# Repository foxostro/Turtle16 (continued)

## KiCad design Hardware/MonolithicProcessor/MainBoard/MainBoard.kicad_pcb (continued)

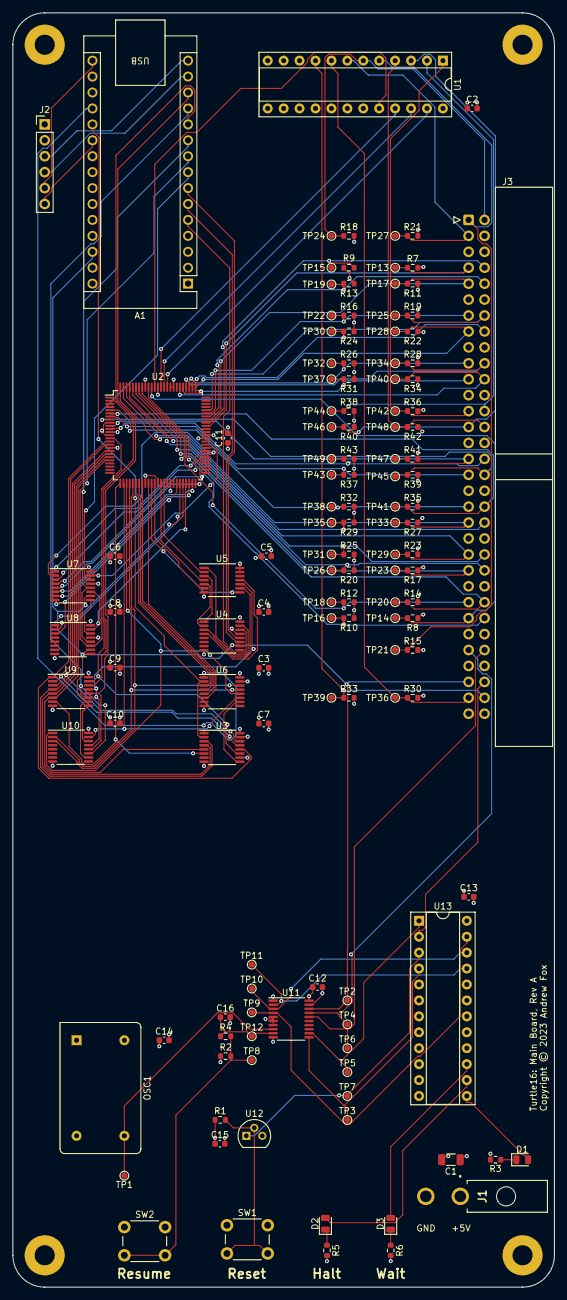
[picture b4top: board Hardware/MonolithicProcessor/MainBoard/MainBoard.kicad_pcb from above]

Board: 4 copper layers, 86.4 x 203.2 mm, 135 parts (0 on the bottom side), 119 nets.

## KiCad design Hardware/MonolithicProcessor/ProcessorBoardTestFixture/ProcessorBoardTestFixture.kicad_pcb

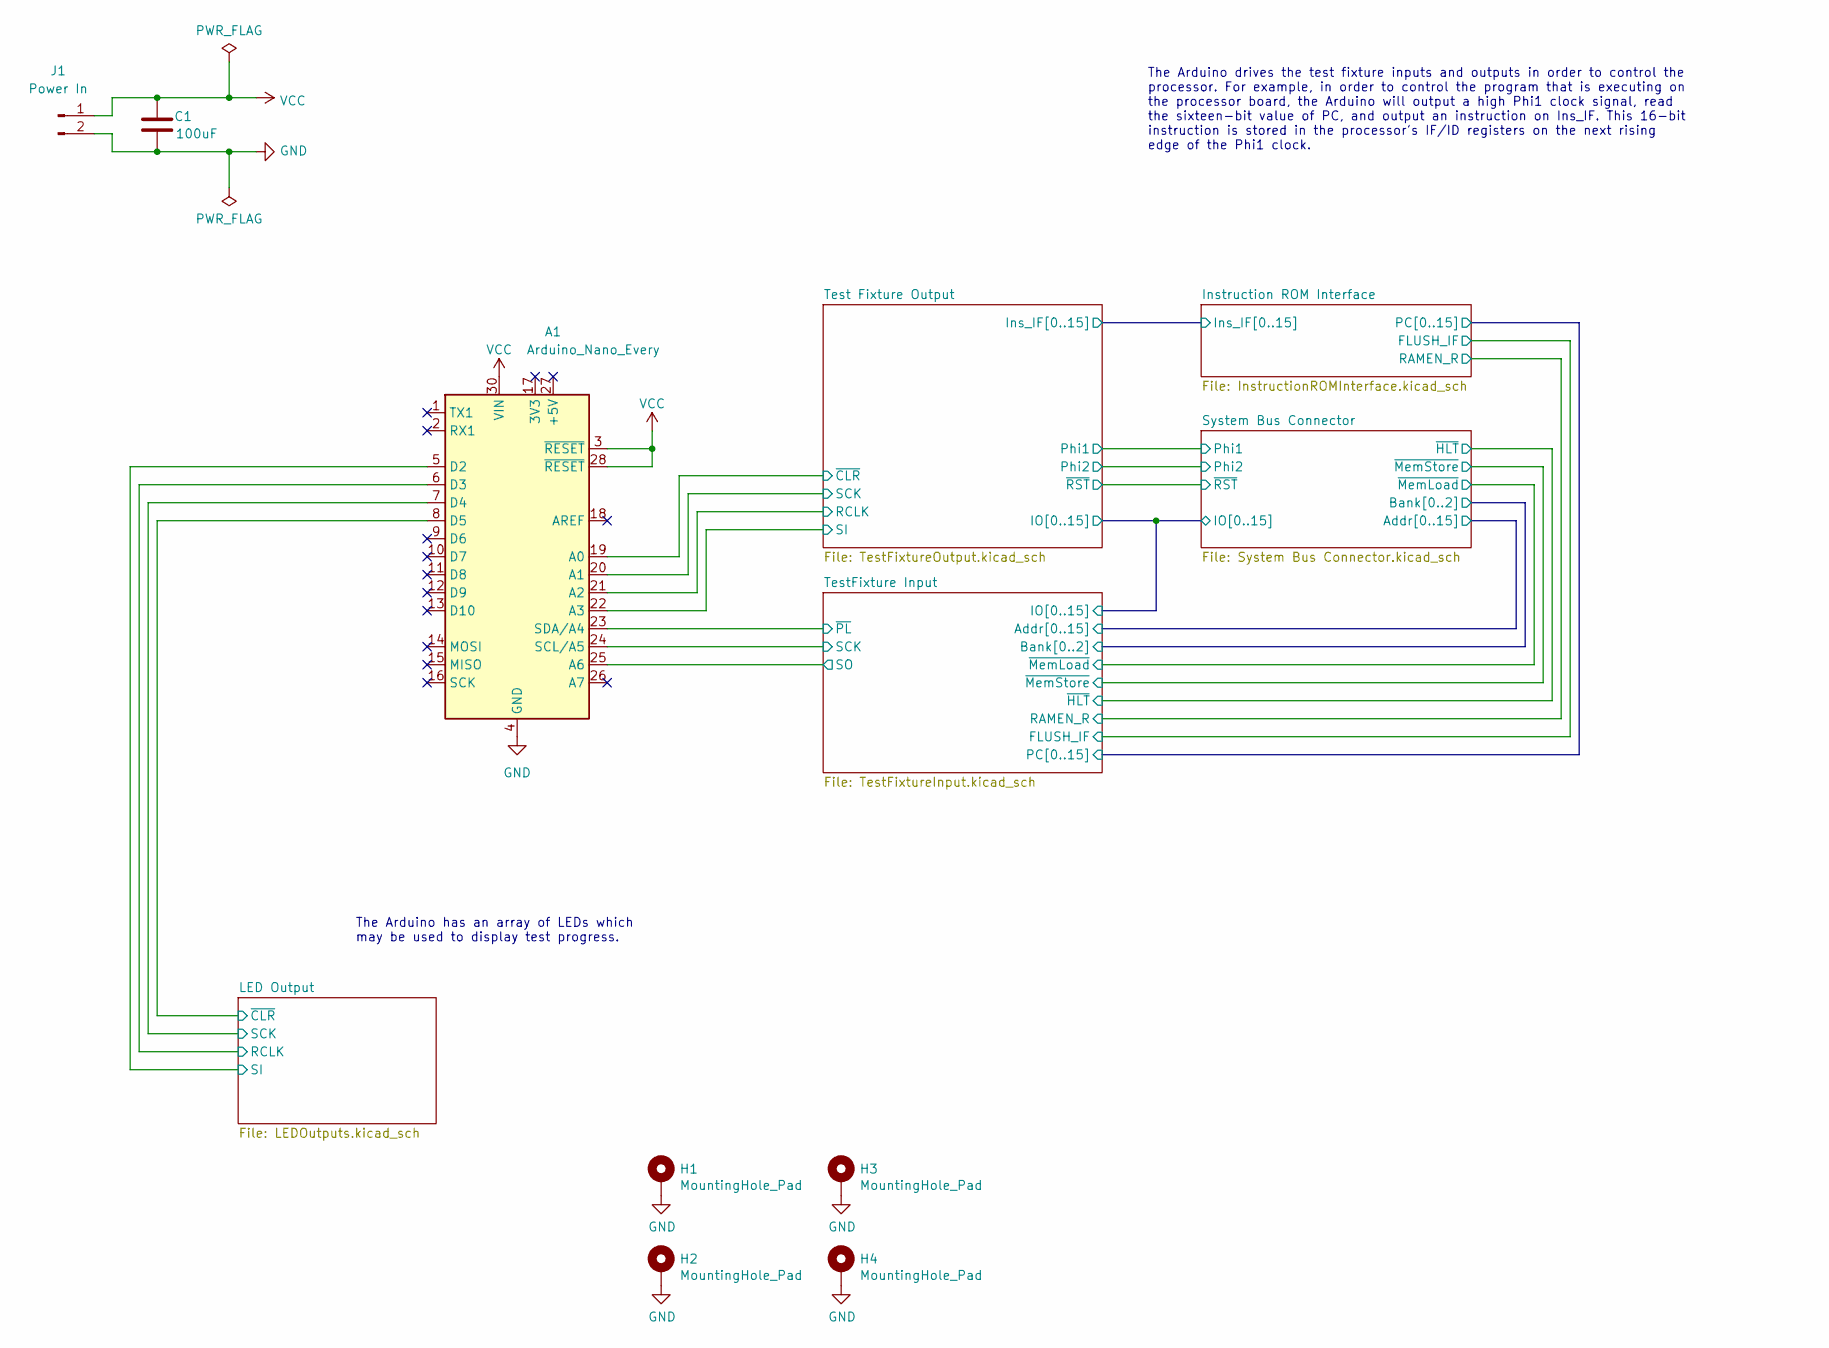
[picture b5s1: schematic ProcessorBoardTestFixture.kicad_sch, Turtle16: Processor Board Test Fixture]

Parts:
A1: Arduino_Nano_Every; Arduino_Nano
C1: 100uF; C_1206_3216Metric; Manufacturer# AMK316ABJ107ML-T; Mouser# 963-AMK316ABJ107ML-T
H1, H2, H3, H4: MountingHole_Pad; MountingHole_3.2mm_M3_Pad
J1: Power In; 172448-0002; Manufacturer# 172448-0002; Mouser# 538-172448-0002

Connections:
/LED Output/RCLK: A1.6 (D3); also elsewhere on the board
/LED Output/SCK: A1.7 (D4); also elsewhere on the board
/LED Output/SI: A1.5 (D2); also elsewhere on the board
/LED Output/~CLR: A1.8 (D5); also elsewhere on the board
/Test Fixture Output/RCLK: A1.21 (A2); also elsewhere on the board
/Test Fixture Output/SCK: A1.20 (A1); also elsewhere on the board
/Test Fixture Output/SI: A1.22 (A3); also elsewhere on the board
/Test Fixture Output/~CLR: A1.19 (A0); also elsewhere on the board
/TestFixture Input/SCK: A1.24 (SCL/A5); also elsewhere on the board
/TestFixture Input/SO: A1.25 (A6); also elsewhere on the board
/TestFixture Input/~PL: A1.23 (SDA/A4); also elsewhere on the board
GND: A1.4 (GND), A1.29 (GND), C1.2, H1.1, H2.1, H3.1, H4.1, J1.2; also elsewhere on the board
VCC: A1.3 (~RESET), A1.28 (~RESET), A1.30 (VIN), C1.1, J1.1; also elsewhere on the board

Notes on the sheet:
The Arduino has an array of LEDs which may be used to display test progress.
The Arduino drives the test fixture inputs and outputs in order to control the processor. For example, in order to control the program that is executing on the processor board, the Arduino will output a high Phi1 clock signal, read the sixteen-bit value of PC, and output an instruction on Ins_IF. T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

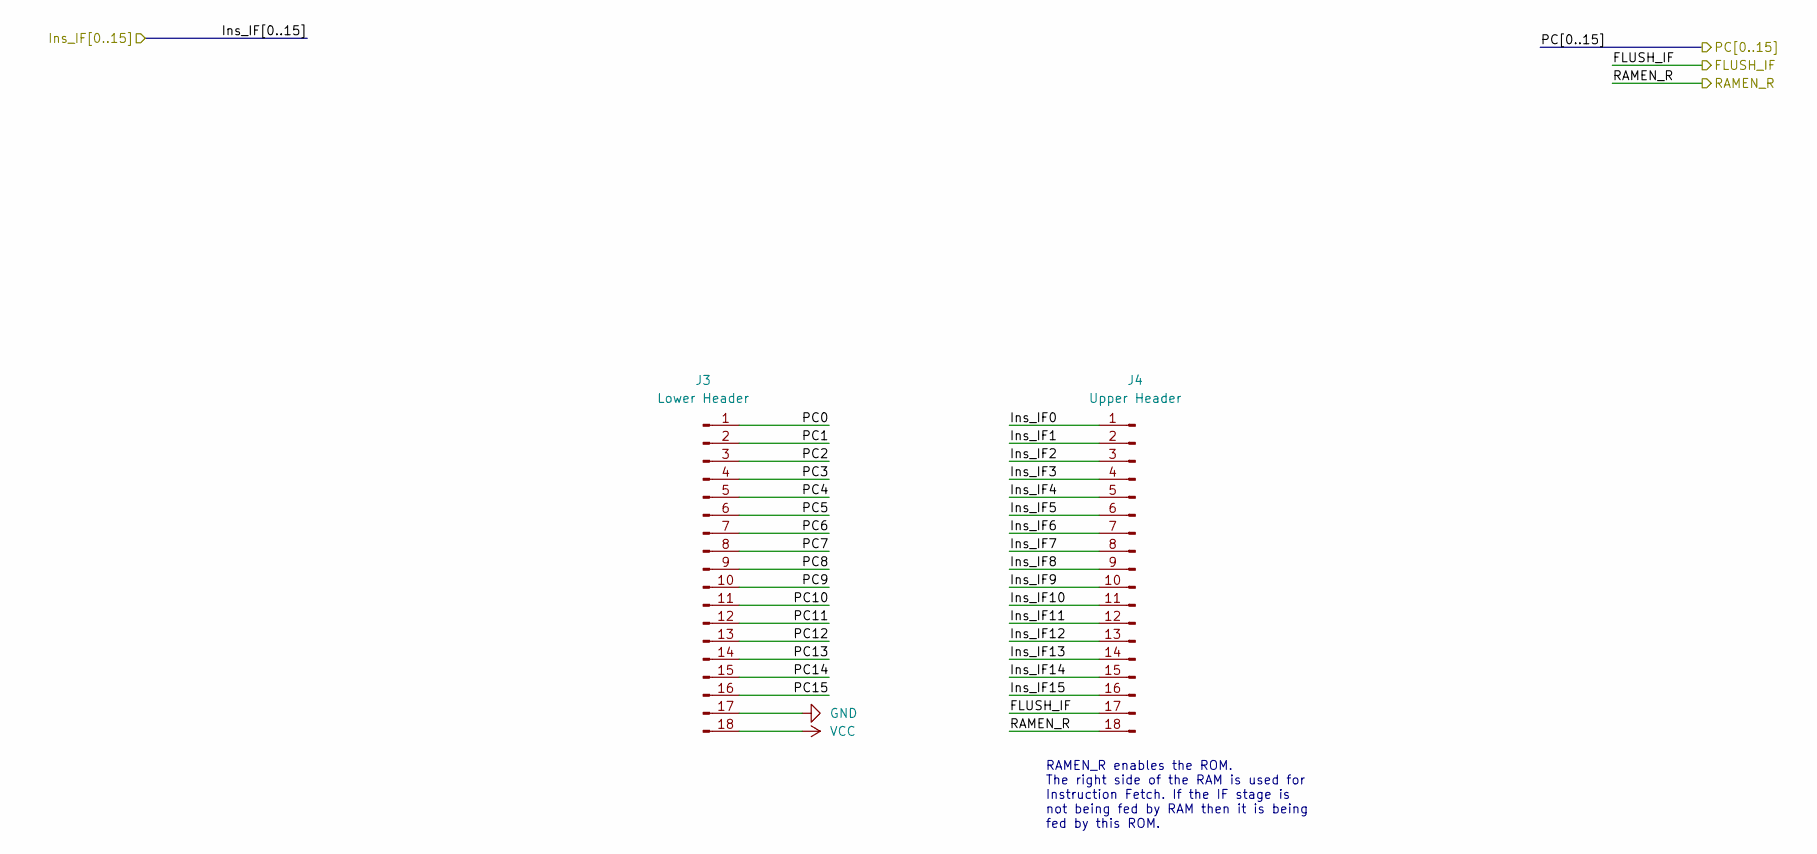
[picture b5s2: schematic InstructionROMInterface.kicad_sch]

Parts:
J3: Lower Header; PinHeader_1x18_P2.54mm_Vertical
J4: Upper Header; PinHeader_1x18_P2.54mm_Vertical

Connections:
/Instruction ROM Interface/FLUSH_IF: J4.17; also elsewhere on the board
/Instruction ROM Interface/Ins_IF0: J4.1; also elsewhere on the board
/Instruction ROM Interface/Ins_IF1: J4.2; also elsewhere on the board
/Instruction ROM Interface/Ins_IF2: J4.3; also elsewhere on the board
/Instruction ROM Interface/Ins_IF3: J4.4; also elsewhere on the board
/Instruction ROM Interface/Ins_IF4: J4.5; also elsewhere on the board
/Instruction ROM Interface/Ins_IF5: J4.6; also elsewhere on the board
/Instruction ROM Interface/Ins_IF6: J4.7; also elsewhere on the board
/Instruction ROM Interface/Ins_IF7: J4.8; also elsewhere on the board
/Instruction ROM Interface/Ins_IF8: J4.9; also elsewhere on the board
/Instruction ROM Interface/Ins_IF9: J4.10; also elsewhere on the board
/Instruction ROM Interface/Ins_IF10: J4.11; also elsewhere on the board
/Instruction ROM Interface/Ins_IF11: J4.12; also elsewhere on the board
/Instruction ROM Interface/Ins_IF12: J4.13; also elsewhere on the board
/Instruction ROM Interface/Ins_IF13: J4.14; also elsewhere on the board
/Instruction ROM Interface/Ins_IF14: J4.15; also elsewhere on the board
/Instruction ROM Interface/Ins_IF15: J4.16; also elsewhere on the board
/Instruction ROM Interface/PC0: J3.1; also elsewhere on the board
/Instruction ROM Interface/PC1: J3.2; also elsewhere on the board
/Instruction ROM Interface/PC2: J3.3; also elsewhere on the board
/Instruction ROM Interface/PC3: J3.4; also elsewhere on the board
/Instruction ROM Interface/PC4: J3.5; also elsewhere on the board
/Instruction ROM Interface/PC5: J3.6; also elsewhere on the board
/Instruction ROM Interface/PC6: J3.7; also elsewhere on the board
/Instruction ROM Interface/PC7: J3.8; also elsewhere on the board
/Instruction ROM Interface/PC8: J3.9; also elsewhere on the board
/Instruction ROM Interface/PC9: J3.10; also elsewhere on the board
/Instruction ROM Interface/PC10: J3.11; also elsewhere on the board
/Instruction ROM Interface/PC11: J3.12; also elsewhere on the board
/Instruction ROM Interface/PC12: J3.13; also elsewhere on the board
/Instruction ROM Interface/PC13: J3.14; also elsewhere on the board
/Instruction ROM Interface/PC14: J3.15; also elsewhere on the board
/Instruction ROM Interface/PC15: J3.16; also elsewhere on the board
/Instruction ROM Interface/RAMEN_R: J4.18; also elsewhere on the board
GND: J3.17; also elsewhere on the board
VCC: J3.18; also elsewhere on the board

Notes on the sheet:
RAMEN_R enables the ROM. The right side of the RAM is used for Instruction Fetch. If the IF stage is not being fed by RAM then it is being fed by this ROM.

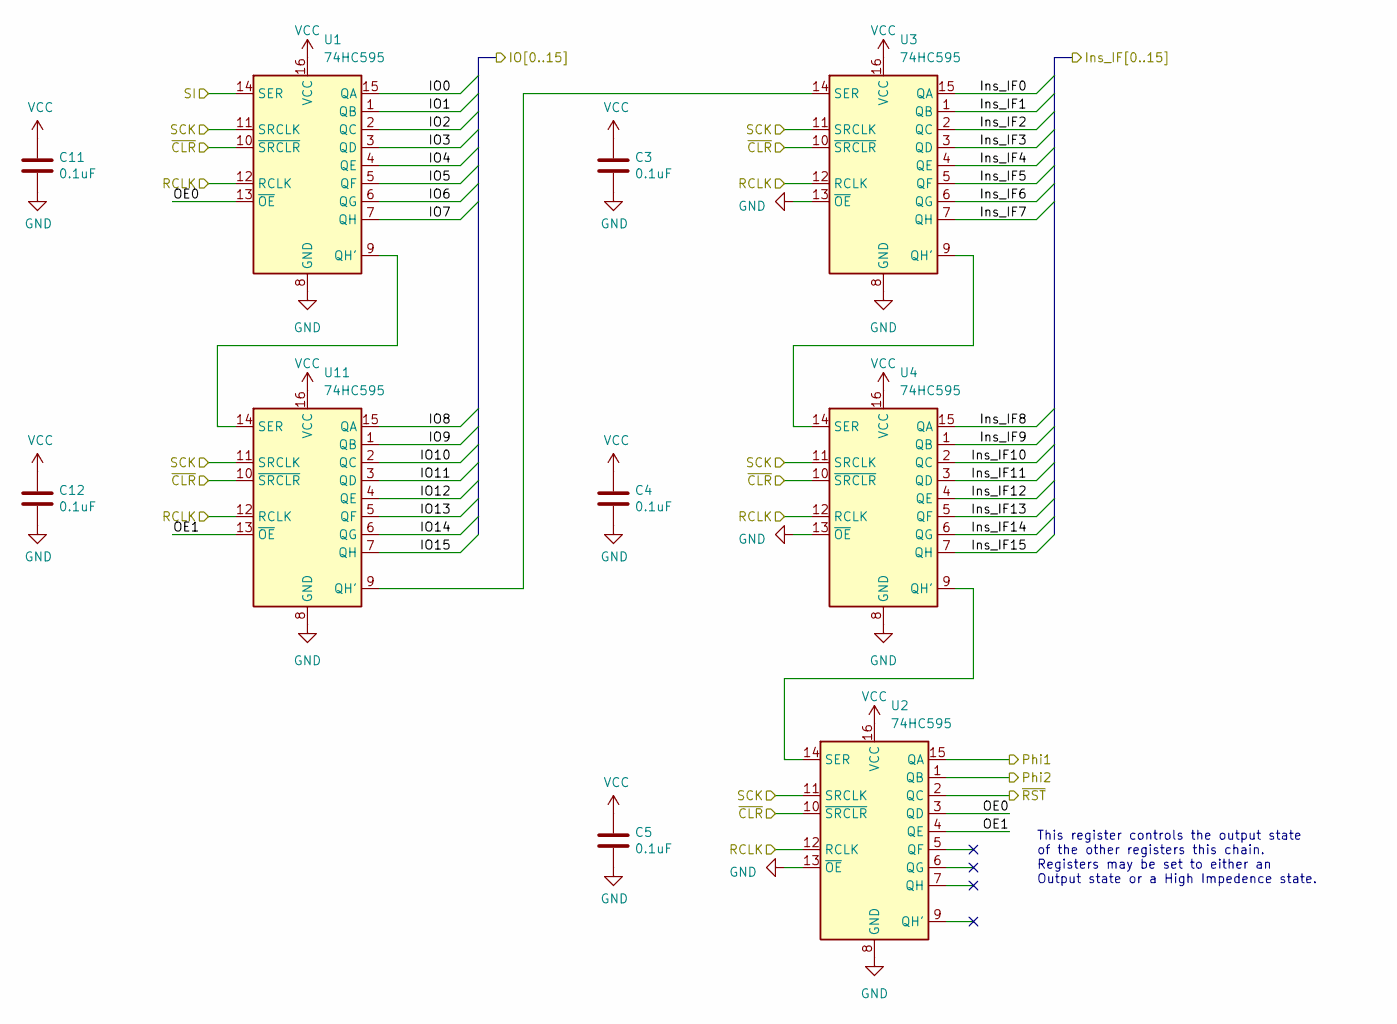
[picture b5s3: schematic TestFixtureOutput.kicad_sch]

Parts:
C3, C4, C5, C11, C12: 0.1uF; C_0603_1608Metric; Manufacturer# EMK107B7104KAHT; Mouser# 963-EMK107B7104KAHT
U1, U2, U3, U4, U11: 74HC595; TSSOP-16_4.4x5mm_P0.65mm; Manufacturer# 74HC595PW-Q100,118; Mouser# 771-74HC595PW-Q100

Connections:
/Instruction ROM Interface/Ins_IF0: U3.15 (QA); also elsewhere on the board
/Instruction ROM Interface/Ins_IF1: U3.1 (QB); also elsewhere on the board
/Instruction ROM Interface/Ins_IF2: U3.2 (QC); also elsewhere on the board
/Instruction ROM Interface/Ins_IF3: U3.3 (QD); also elsewhere on the board
/Instruction ROM Interface/Ins_IF4: U3.4 (QE); also elsewhere on the board
/Instruction ROM Interface/Ins_IF5: U3.5 (QF); also elsewhere on the board
/Instruction ROM Interface/Ins_IF6: U3.6 (QG); also elsewhere on the board
/Instruction ROM Interface/Ins_IF7: U3.7 (QH); also elsewhere on the board
/Instruction ROM Interface/Ins_IF8: U4.15 (QA); also elsewhere on the board
/Instruction ROM Interface/Ins_IF9: U4.1 (QB); also elsewhere on the board
/Instruction ROM Interface/Ins_IF10: U4.2 (QC); also elsewhere on the board
/Instruction ROM Interface/Ins_IF11: U4.3 (QD); also elsewhere on the board
/Instruction ROM Interface/Ins_IF12: U4.4 (QE); also elsewhere on the board
/Instruction ROM Interface/Ins_IF13: U4.5 (QF); also elsewhere on the board
/Instruction ROM Interface/Ins_IF14: U4.6 (QG); also elsewhere on the board
/Instruction ROM Interface/Ins_IF15: U4.7 (QH); also elsewhere on the board
/System Bus Connector/IO0: U1.15 (QA); also elsewhere on the board
/System Bus Connector/IO1: U1.1 (QB); also elsewhere on the board
/System Bus Connector/IO2: U1.2 (QC); also elsewhere on the board
/System Bus Connector/IO3: U1.3 (QD); also elsewhere on the board
/System Bus Connector/IO4: U1.4 (QE); also elsewhere on the board
/System Bus Connector/IO5: U1.5 (QF); also elsewhere on the board
/System Bus Connector/IO6: U1.6 (QG); also elsewhere on the board
/System Bus Connector/IO7: U1.7 (QH); also elsewhere on the board
/System Bus Connector/IO8: U11.15 (QA); also elsewhere on the board
/System Bus Connector/IO9: U11.1 (QB); also elsewhere on the board
/System Bus Connector/IO10: U11.2 (QC); also elsewhere on the board
/System Bus Connector/IO11: U11.3 (QD); also elsewhere on the board
/System Bus Connector/IO12: U11.4 (QE); also elsewhere on the board
/System Bus Connector/IO13: U11.5 (QF); also elsewhere on the board
/System Bus Connector/IO14: U11.6 (QG); also elsewhere on the board
/System Bus Connector/IO15: U11.7 (QH); also elsewhere on the board
/System Bus Connector/Phi1: U2.15 (QA); also elsewhere on the board
/System Bus Connector/Phi2: U2.1 (QB); also elsewhere on the board
/System Bus Connector/~RST: U2.2 (QC); also elsewhere on the board
/Test Fixture Output/OE0: U1.13 (~OE), U2.3 (QD)
/Test Fixture Output/OE1: U2.4 (QE), U11.13 (~OE)
/Test Fixture Output/RCLK: U1.12 (RCLK), U2.12 (RCLK), U3.12 (RCLK), U4.12 (RCLK), U11.12 (RCLK); also elsewhere on the board
/Test Fixture Output/SCK: U1.11 (SRCLK), U2.11 (SRCLK), U3.11 (SRCLK), U4.11 (SRCLK), U11.11 (SRCLK); also elsewhere on the board
/Test Fixture Output/SI: U1.14 (SER); also elsewhere on the board
/Test Fixture Output/~CLR: U1.10 (~SRCLR), U2.10 (~SRCLR), U3.10 (~SRCLR), U4.10 (~SRCLR), U11.10 (~SRCLR); also elsewhere on the board
GND: C3.2, C4.2, C5.2, C11.2, C12.2, U1.8 (GND), U2.8 (GND), U2.13 (~OE), U3.8 (GND), U3.13 (~OE), U4.8 (GND), U4.13 (~OE), U11.8 (GND); also elsewhere on the board
unnamed: U1.9 (QH'), U11.14 (SER)
unnamed: U2.14 (SER), U4.9 (QH')
unnamed: U3.9 (QH'), U4.14 (SER)
unnamed: U3.14 (SER), U11.9 (QH')
VCC: C3.1, C4.1, C5.1, C11.1, C12.1, U1.16 (VCC), U2.16 (VCC), U3.16 (VCC), U4.16 (VCC), U11.16 (VCC); also elsewhere on the board

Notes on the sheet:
This register controls the output state of the other registers this chain. Registers may be set to either an Output state or a High Impedence state.

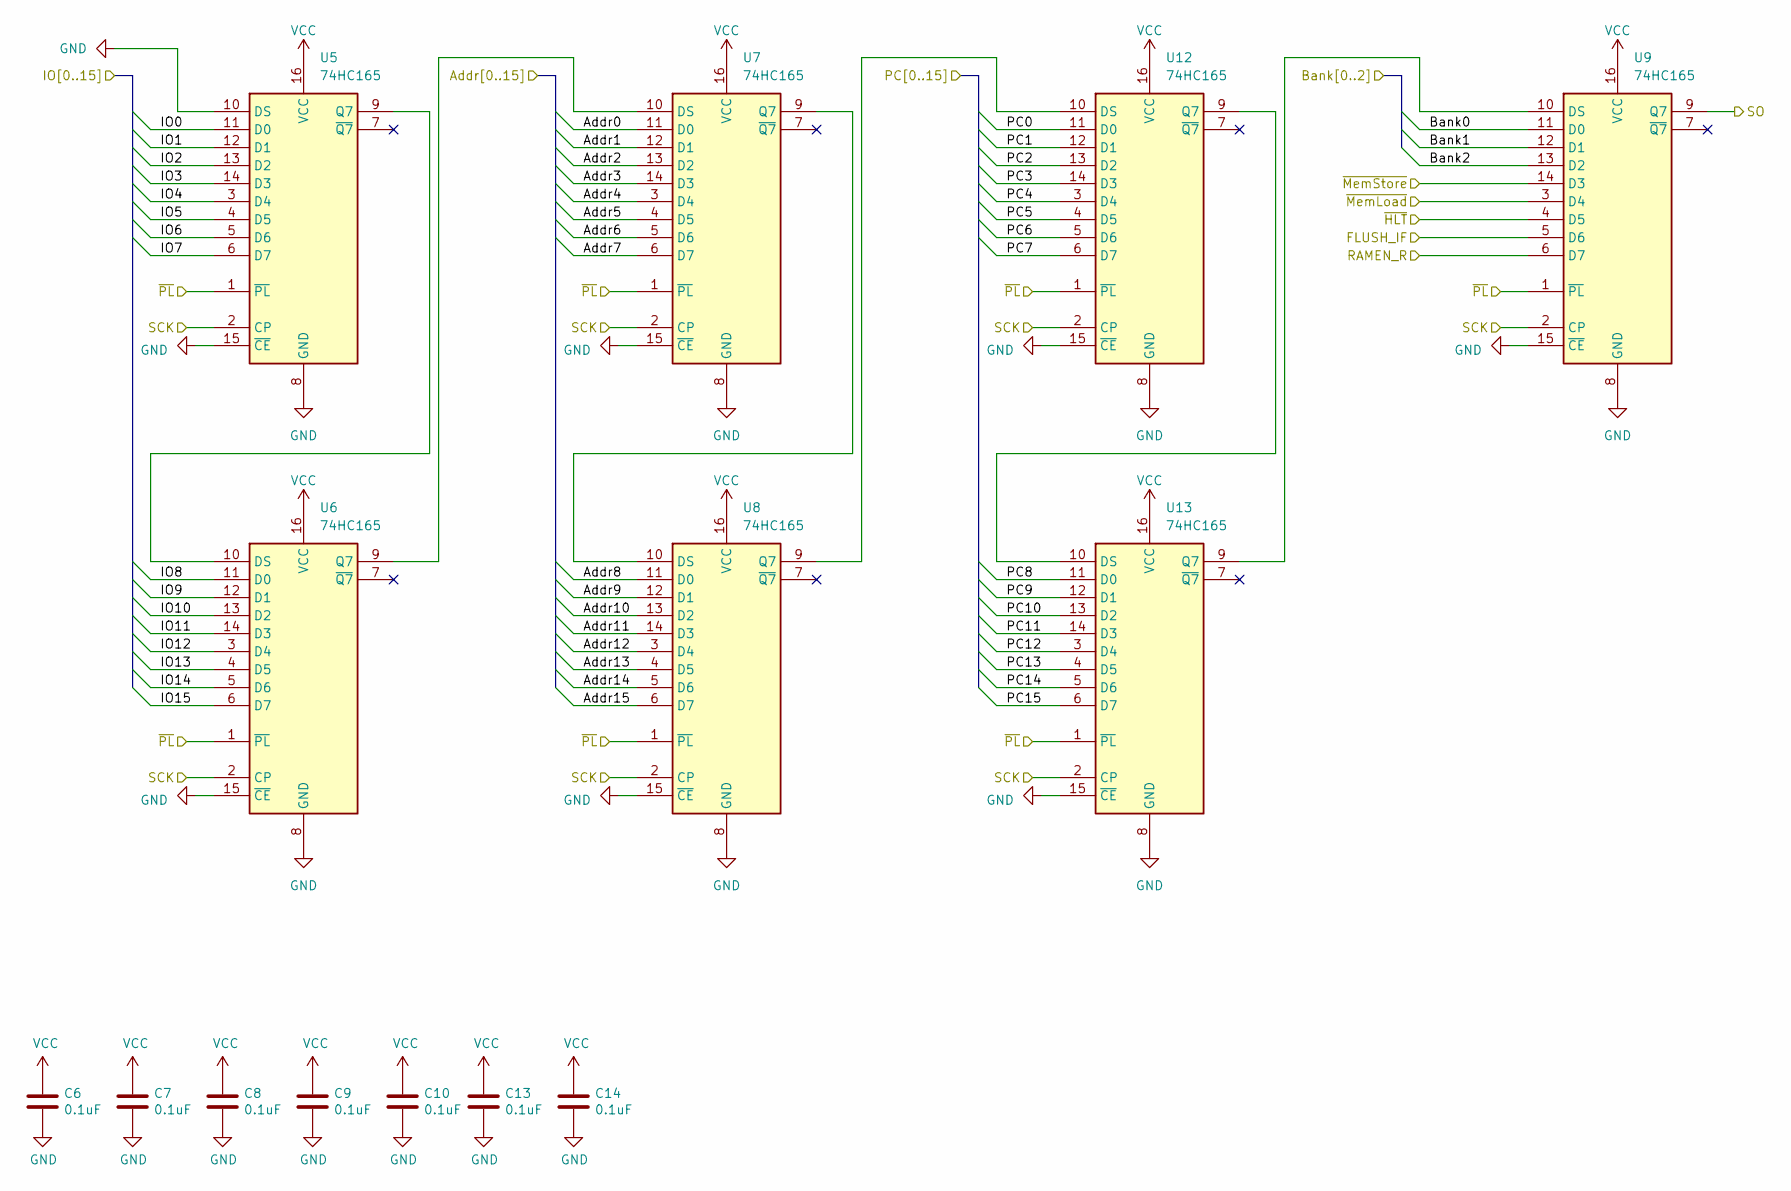
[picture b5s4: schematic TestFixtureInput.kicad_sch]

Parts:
C6, C7, C8, C9, C10, C13, C14: 0.1uF; C_0603_1608Metric; Manufacturer# EMK107B7104KAHT; Mouser# 963-EMK107B7104KAHT
U5, U6, U7, U8, U9, U12, U13: 74HC165; TSSOP-16_4.4x5mm_P0.65mm; Manufacturer# 74HC165PW-Q100,118; Mouser# 771-74HC165PWQ100118

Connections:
/Instruction ROM Interface/FLUSH_IF: U9.5 (D6); also elsewhere on the board
/Instruction ROM Interface/PC0: U12.11 (D0); also elsewhere on the board
/Instruction ROM Interface/PC1: U12.12 (D1); also elsewhere on the board
/Instruction ROM Interface/PC2: U12.13 (D2); also elsewhere on the board
/Instruction ROM Interface/PC3: U12.14 (D3); also elsewhere on the board
/Instruction ROM Interface/PC4: U12.3 (D4); also elsewhere on the board
/Instruction ROM Interface/PC5: U12.4 (D5); also elsewhere on the board
/Instruction ROM Interface/PC6: U12.5 (D6); also elsewhere on the board
/Instruction ROM Interface/PC7: U12.6 (D7); also elsewhere on the board
/Instruction ROM Interface/PC8: U13.11 (D0); also elsewhere on the board
/Instruction ROM Interface/PC9: U13.12 (D1); also elsewhere on the board
/Instruction ROM Interface/PC10: U13.13 (D2); also elsewhere on the board
/Instruction ROM Interface/PC11: U13.14 (D3); also elsewhere on the board
/Instruction ROM Interface/PC12: U13.3 (D4); also elsewhere on the board
/Instruction ROM Interface/PC13: U13.4 (D5); also elsewhere on the board
/Instruction ROM Interface/PC14: U13.5 (D6); also elsewhere on the board
/Instruction ROM Interface/PC15: U13.6 (D7); also elsewhere on the board
/Instruction ROM Interface/RAMEN_R: U9.6 (D7); also elsewhere on the board
/System Bus Connector/Addr0: U7.11 (D0); also elsewhere on the board
/System Bus Connector/Addr1: U7.12 (D1); also elsewhere on the board
/System Bus Connector/Addr2: U7.13 (D2); also elsewhere on the board
/System Bus Connector/Addr3: U7.14 (D3); also elsewhere on the board
/System Bus Connector/Addr4: U7.3 (D4); also elsewhere on the board
/System Bus Connector/Addr5: U7.4 (D5); also elsewhere on the board
/System Bus Connector/Addr6: U7.5 (D6); also elsewhere on the board
/System Bus Connector/Addr7: U7.6 (D7); also elsewhere on the board
/System Bus Connector/Addr8: U8.11 (D0); also elsewhere on the board
/System Bus Connector/Addr9: U8.12 (D1); also elsewhere on the board
/System Bus Connector/Addr10: U8.13 (D2); also elsewhere on the board
/System Bus Connector/Addr11: U8.14 (D3); also elsewhere on the board
/System Bus Connector/Addr12: U8.3 (D4); also elsewhere on the board
/System Bus Connector/Addr13: U8.4 (D5); also elsewhere on the board
/System Bus Connector/Addr14: U8.5 (D6); also elsewhere on the board
/System Bus Connector/Addr15: U8.6 (D7); also elsewhere on the board
/System Bus Connector/Bank0: U9.11 (D0); also elsewhere on the board
/System Bus Connector/Bank1: U9.12 (D1); also elsewhere on the board
/System Bus Connector/Bank2: U9.13 (D2); also elsewhere on the board
/System Bus Connector/IO0: U5.11 (D0); also elsewhere on the board
/System Bus Connector/IO1: U5.12 (D1); also elsewhere on the board
/System Bus Connector/IO2: U5.13 (D2); also elsewhere on the board
/System Bus Connector/IO3: U5.14 (D3); also elsewhere on the board
/System Bus Connector/IO4: U5.3 (D4); also elsewhere on the board
/System Bus Connector/IO5: U5.4 (D5); also elsewhere on the board
/System Bus Connector/IO6: U5.5 (D6); also elsewhere on the board
/System Bus Connector/IO7: U5.6 (D7); also elsewhere on the board
/System Bus Connector/IO8: U6.11 (D0); also elsewhere on the board
/System Bus Connector/IO9: U6.12 (D1); also elsewhere on the board
/System Bus Connector/IO10: U6.13 (D2); also elsewhere on the board
/System Bus Connector/IO11: U6.14 (D3); also elsewhere on the board
/System Bus Connector/IO12: U6.3 (D4); also elsewhere on the board
/System Bus Connector/IO13: U6.4 (D5); also elsewhere on the board
/System Bus Connector/IO14: U6.5 (D6); also elsewhere on the board
/System Bus Connector/IO15: U6.6 (D7); also elsewhere on the board
/System Bus Connector/~HLT: U9.4 (D5); also elsewhere on the board
/System Bus Connector/~MemLoad: U9.3 (D4); also elsewhere on the board
/System Bus Connector/~MemStore: U9.14 (D3); also elsewhere on the board
/TestFixture Input/SCK: U5.2 (CP), U6.2 (CP), U7.2 (CP), U8.2 (CP), U9.2 (CP), U12.2 (CP), U13.2 (CP); also elsewhere on the board
/TestFixture Input/SO: U9.9 (Q7); also elsewhere on the board
/TestFixture Input/~PL: U5.1 (~PL), U6.1 (~PL), U7.1 (~PL), U8.1 (~PL), U9.1 (~PL), U12.1 (~PL), U13.1 (~PL); also elsewhere on the board
GND: C6.2, C7.2, C8.2, C9.2, C10.2, C13.2, C14.2, U5.8 (GND), U5.10 (DS), U5.15 (~CE), U6.8 (GND), U6.15 (~CE), U7.8 (GND), U7.15 (~CE), U8.8 (GND), U8.15 (~CE), U9.8 (GND), U9.15 (~CE), U12.8 (GND), U12.15 (~CE), U13.8 (GND), U13.15 (~CE); also elsewhere on the board
unnamed: U5.9 (Q7), U6.10 (DS)
unnamed: U6.9 (Q7), U7.10 (DS)
unnamed: U7.9 (Q7), U8.10 (DS)
unnamed: U8.9 (Q7), U12.10 (DS)
unnamed: U12.9 (Q7), U13.10 (DS)
unnamed: U9.10 (DS), U13.9 (Q7)
VCC: C6.1, C7.1, C8.1, C9.1, C10.1, C13.1, C14.1, U5.16 (VCC), U6.16 (VCC), U7.16 (VCC), U8.16 (VCC), U9.16 (VCC), U12.16 (VCC), U13.16 (VCC); also elsewhere on the board

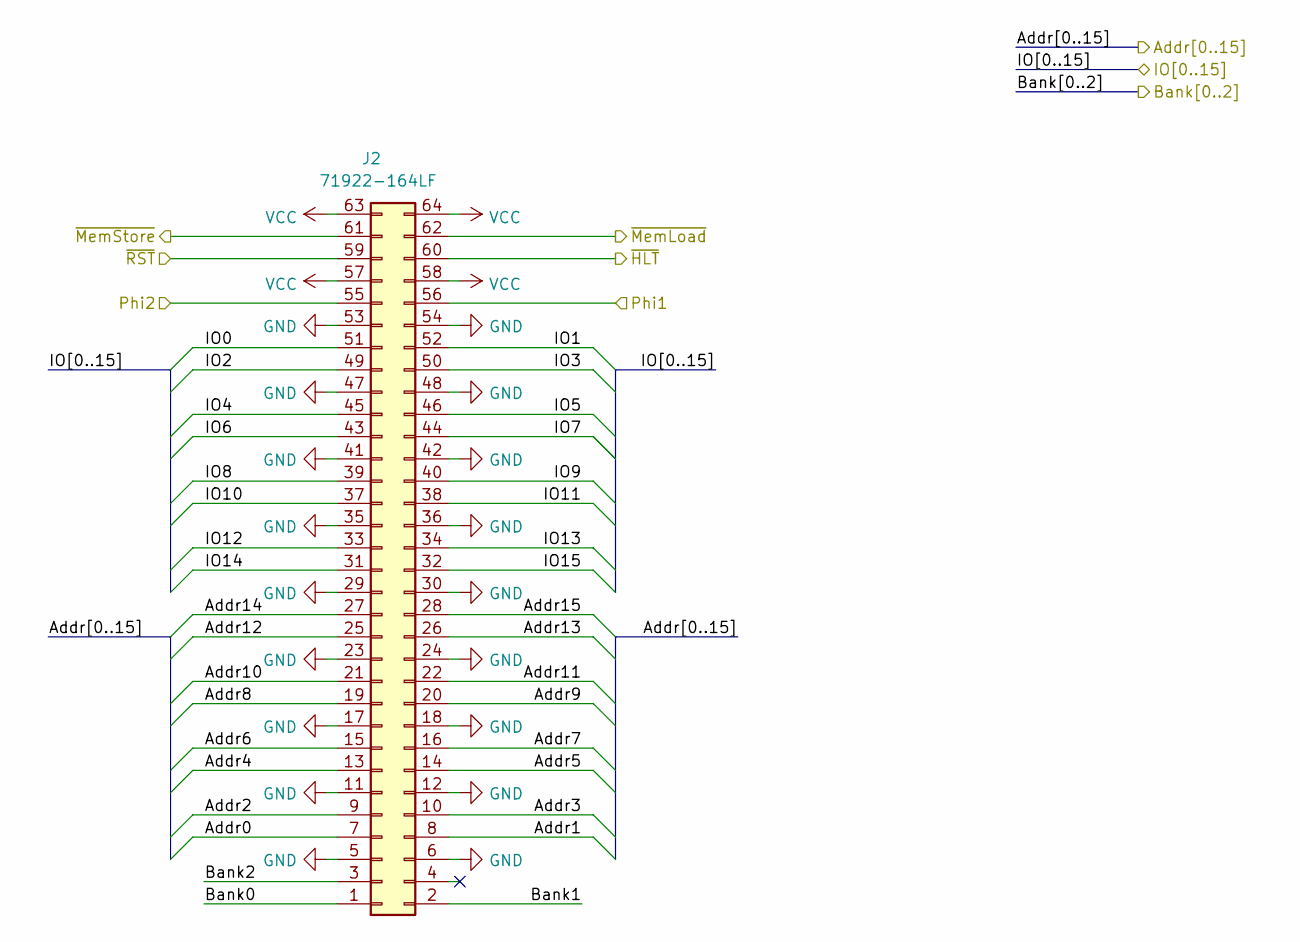
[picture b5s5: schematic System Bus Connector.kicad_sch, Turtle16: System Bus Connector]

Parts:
J2: 71922-164LF; IDC-Header_2x32_P2.54mm_Horizontal; Manufacturer# 71922-164LF; Mouser# 649-71922-164LF

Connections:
/System Bus Connector/Addr0: J2.7; also elsewhere on the board
/System Bus Connector/Addr1: J2.8; also elsewhere on the board
/System Bus Connector/Addr2: J2.9; also elsewhere on the board
/System Bus Connector/Addr3: J2.10; also elsewhere on the board
/System Bus Connector/Addr4: J2.13; also elsewhere on the board
/System Bus Connector/Addr5: J2.14; also elsewhere on the board
/System Bus Connector/Addr6: J2.15; also elsewhere on the board
/System Bus Connector/Addr7: J2.16; also elsewhere on the board
/System Bus Connector/Addr8: J2.19; also elsewhere on the board
/System Bus Connector/Addr9: J2.20; also elsewhere on the board
/System Bus Connector/Addr10: J2.21; also elsewhere on the board
/System Bus Connector/Addr11: J2.22; also elsewhere on the board
/System Bus Connector/Addr12: J2.25; also elsewhere on the board
/System Bus Connector/Addr13: J2.26; also elsewhere on the board
/System Bus Connector/Addr14: J2.27; also elsewhere on the board
/System Bus Connector/Addr15: J2.28; also elsewhere on the board
/System Bus Connector/Bank0: J2.1; also elsewhere on the board
/System Bus Connector/Bank1: J2.2; also elsewhere on the board
/System Bus Connector/Bank2: J2.3; also elsewhere on the board
/System Bus Connector/IO0: J2.51; also elsewhere on the board
/System Bus Connector/IO1: J2.52; also elsewhere on the board
/System Bus Connector/IO2: J2.49; also elsewhere on the board
/System Bus Connector/IO3: J2.50; also elsewhere on the board
/System Bus Connector/IO4: J2.45; also elsewhere on the board
/System Bus Connector/IO5: J2.46; also elsewhere on the board
/System Bus Connector/IO6: J2.43; also elsewhere on the board
/System Bus Connector/IO7: J2.44; also elsewhere on the board
/System Bus Connector/IO8: J2.39; also elsewhere on the board
/System Bus Connector/IO9: J2.40; also elsewhere on the board
/System Bus Connector/IO10: J2.37; also elsewhere on the board
/System Bus Connector/IO11: J2.38; also elsewhere on the board
/System Bus Connector/IO12: J2.33; also elsewhere on the board
/System Bus Connector/IO13: J2.34; also elsewhere on the board
/System Bus Connector/IO14: J2.31; also elsewhere on the board
/System Bus Connector/IO15: J2.32; also elsewhere on the board
/System Bus Connector/Phi1: J2.56; also elsewhere on the board
/System Bus Connector/Phi2: J2.55; also elsewhere on the board
/System Bus Connector/~HLT: J2.60; also elsewhere on the board
/System Bus Connector/~MemLoad: J2.62; also elsewhere on the board
/System Bus Connector/~MemStore: J2.61; also elsewhere on the board
/System Bus Connector/~RST: J2.59; also elsewhere on the board
GND: J2.5, J2.6, J2.11, J2.12, J2.17, J2.18, J2.23, J2.24, J2.29, J2.30, J2.35, J2.36, J2.41, J2.42, J2.47, J2.48, J2.53, J2.54; also elsewhere on the board
VCC: J2.57, J2.58, J2.63, J2.64; also elsewhere on the board

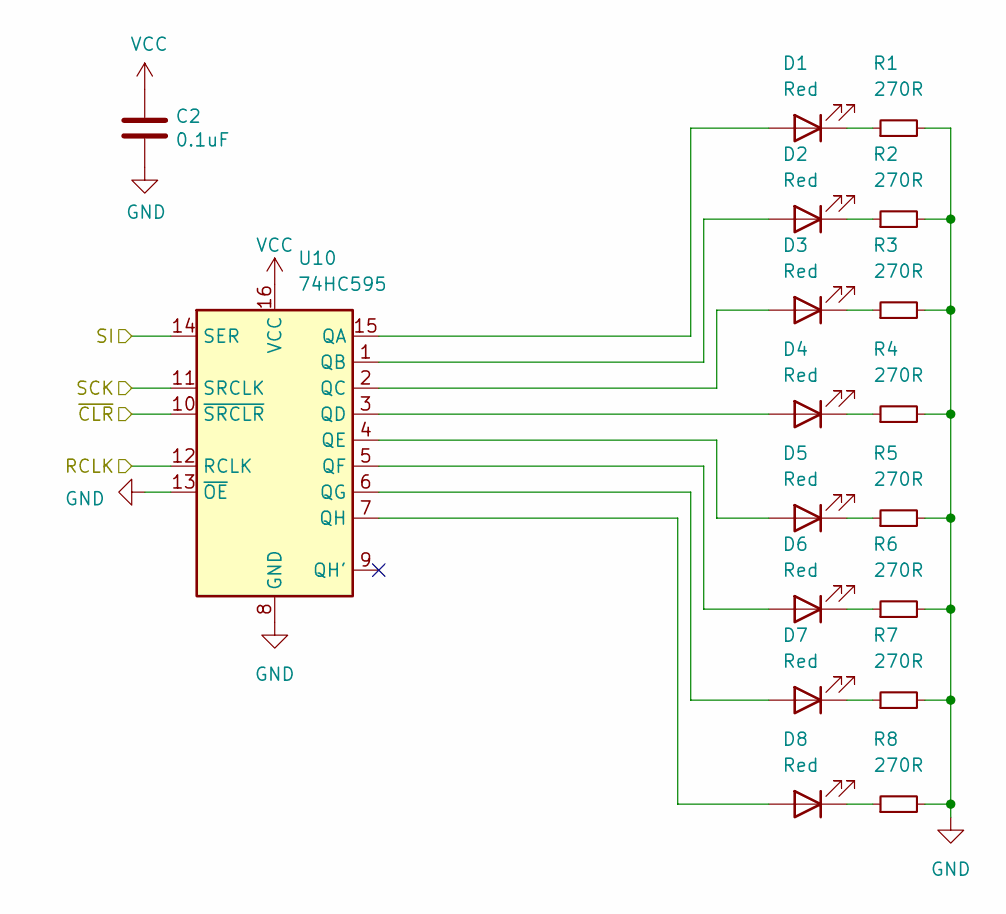
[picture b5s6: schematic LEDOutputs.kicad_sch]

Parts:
C2: 0.1uF; C_0603_1608Metric; Manufacturer# EMK107B7104KAHT; Mouser# 963-EMK107B7104KAHT
D1, D2, D3, D4, D5, D6, D7, D8: Red; LED_0805_2012Metric; Manufacturer# AP2012ID; Mouser# 604-AP2012ID
R1, R2, R3, R4, R5, R6, R7, R8: 270R; R_0603_1608Metric; Manufacturer# CR0603-FX-2700ELF; Mouser# 652-CR0603FX-2700ELF
U10: 74HC595; TSSOP-16_4.4x5mm_P0.65mm; Manufacturer# 74HC595PW-Q100,118; Mouser# 771-74HC595PW-Q100

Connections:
/LED Output/RCLK: U10.12 (RCLK); also elsewhere on the board
/LED Output/SCK: U10.11 (SRCLK); also elsewhere on the board
/LED Output/SI: U10.14 (SER); also elsewhere on the board
/LED Output/~CLR: U10.10 (~SRCLR); also elsewhere on the board
GND: C2.2, R1.2, R2.2, R3.2, R4.2, R5.2, R6.2, R7.2, R8.2, U10.8 (GND), U10.13 (~OE); also elsewhere on the board
unnamed: D1.2 (A), U10.15 (QA)
unnamed: D1.1 (K), R1.1
unnamed: D2.2 (A), U10.1 (QB)
unnamed: D2.1 (K), R2.1
unnamed: D3.2 (A), U10.2 (QC)
unnamed: D3.1 (K), R3.1
unnamed: D4.2 (A), U10.3 (QD)
unnamed: D4.1 (K), R4.1
unnamed: D5.2 (A), U10.4 (QE)
unnamed: D5.1 (K), R5.1
unnamed: D6.2 (A), U10.5 (QF)
unnamed: D6.1 (K), R6.1
unnamed: D7.2 (A), U10.6 (QG)
unnamed: D7.1 (K), R7.1
unnamed: D8.2 (A), U10.7 (QH)
unnamed: D8.1 (K), R8.1
VCC: C2.1, U10.16 (VCC); also elsewhere on the board

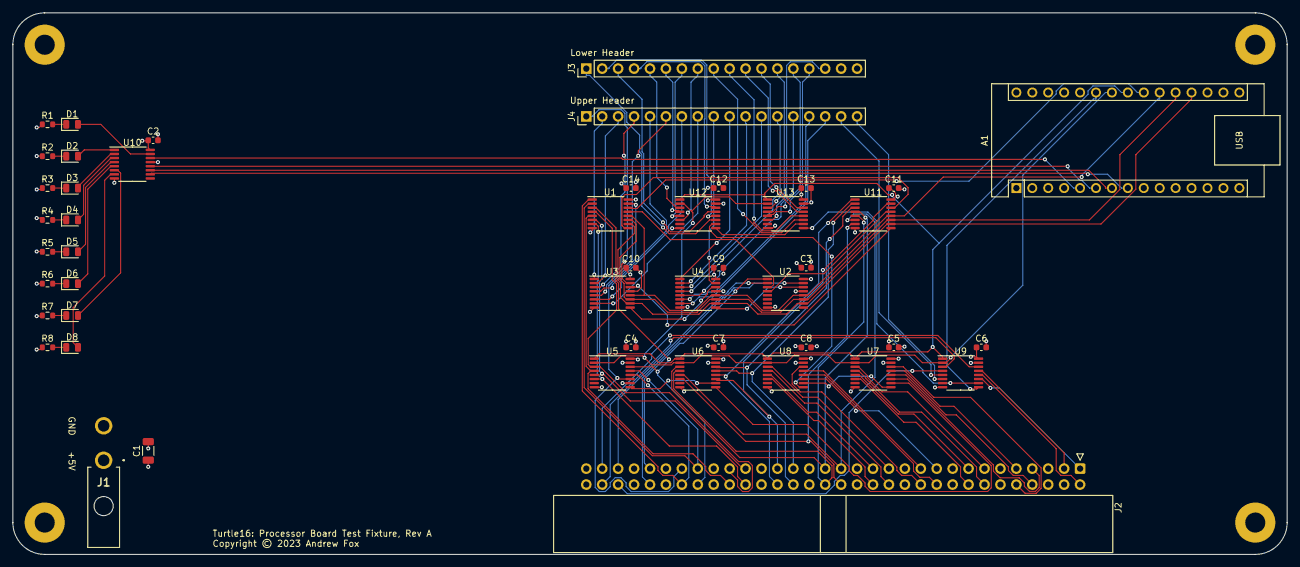
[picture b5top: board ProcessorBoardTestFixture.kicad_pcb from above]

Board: 4 copper layers, 203.2 x 86.4 mm, 52 parts (0 on the bottom side), 116 nets.
